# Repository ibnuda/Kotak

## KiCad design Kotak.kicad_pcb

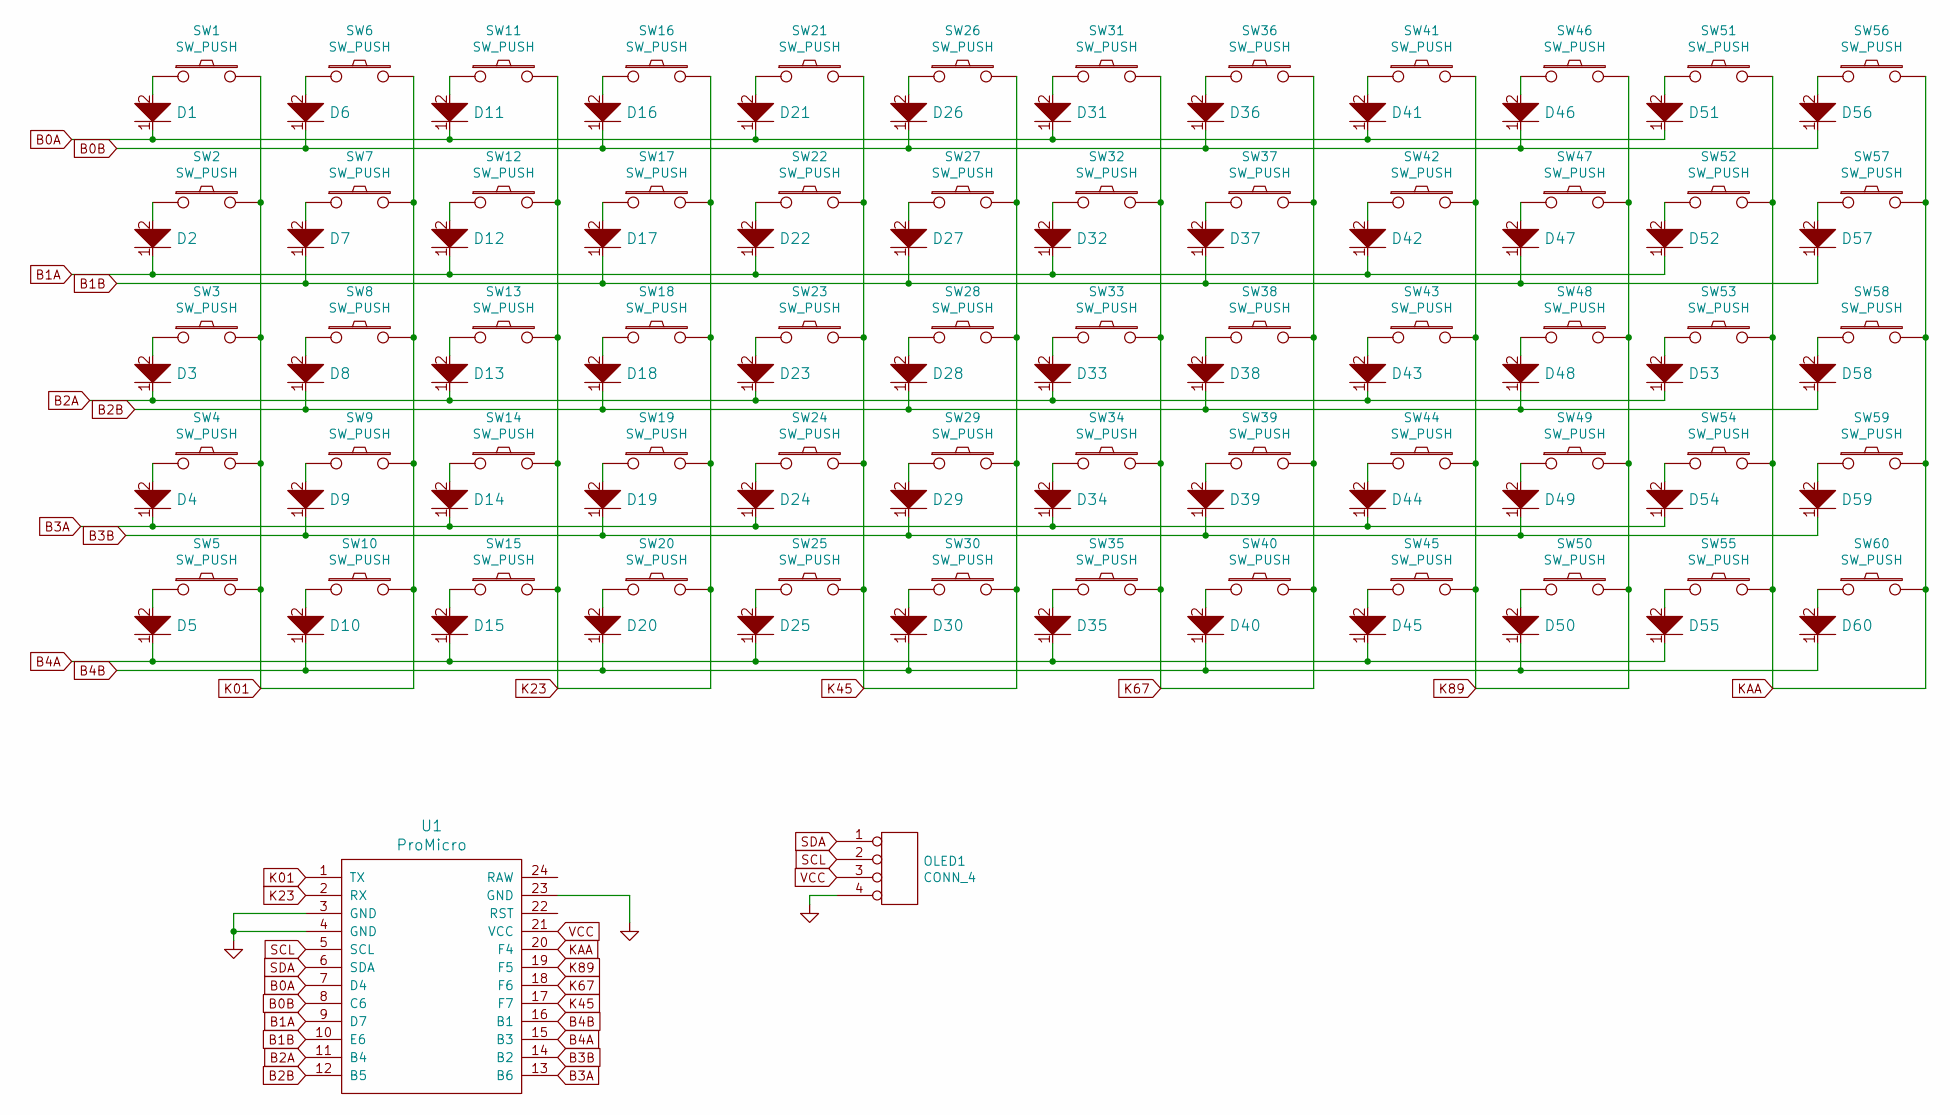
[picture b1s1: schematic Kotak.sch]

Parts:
D1, D2, D3, D4, D5, D6, D7, D8, D9, D10, D11, D12, D13, D14, D15, D16, D17, D18, D19, D20, D21, D22, D23, D24, D25, D26, D27, D28, D29, D30, D31, D32, D33, D34, D35, D36, D37, D38, D39, D40, D41, D42, D43, D44, D45, D46, D47, D48, D49, D50, D51, D52, D53, D54, D55, D56, D57, D58, D59, D60: D; Diode
OLED1: CONN_4; 1X04_NO_SILK
SW1, SW2, SW3, SW4, SW5, SW6, SW7, SW8, SW9, SW10, SW11, SW12, SW13, SW14, SW15, SW16, SW17, SW18, SW19, SW20, SW21, SW22, SW23, SW24, SW25, SW26, SW27, SW28, SW29, SW30, SW31, SW32, SW33, SW34, SW35, SW36, SW37, SW38, SW39, SW40, SW41, SW42, SW43, SW44, SW45, SW46, SW47, SW48, SW49, SW50, SW51, SW52, SW53, SW54, SW55, SW56, SW57, SW58, SW59, SW60: SW_PUSH; MX_Plate_100H
U1: ProMicro; ArduinoProMicro-ZigZag

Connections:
B0A: D1.1, D11.1, D21.1, D31.1, D41.1, D51.1, U1.7 (D4)
B0B: D6.1, D16.1, D26.1, D36.1, D46.1, D56.1, U1.8 (C6)
B1A: D2.1, D12.1, D22.1, D32.1, D42.1, D52.1, U1.9 (D7)
B1B: D7.1, D17.1, D27.1, D37.1, D47.1, D57.1, U1.10 (E6)
B2A: D3.1, D13.1, D23.1, D33.1, D43.1, D53.1, U1.11 (B4)
B2B: D8.1, D18.1, D28.1, D38.1, D48.1, D58.1, U1.12 (B5)
B3A: D4.1, D14.1, D24.1, D34.1, D44.1, D54.1, U1.13 (B6)
B3B: D9.1, D19.1, D29.1, D39.1, D49.1, D59.1, U1.14 (B2)
B4A: D5.1, D15.1, D25.1, D35.1, D45.1, D55.1, U1.15 (B3)
B4B: D10.1, D20.1, D30.1, D40.1, D50.1, D60.1, U1.16 (B1)
GND: OLED1.4, U1.3 (GND), U1.4 (GND), U1.23 (GND)
K01: SW1.2, SW2.2, SW3.2, SW4.2, SW5.2, SW6.2, SW7.2, SW8.2, SW9.2, SW10.2, U1.1 (TX)
K23: SW11.2, SW12.2, SW13.2, SW14.2, SW15.2, SW16.2, SW17.2, SW18.2, SW19.2, SW20.2, U1.2 (RX)
K45: SW21.2, SW22.2, SW23.2, SW24.2, SW25.2, SW26.2, SW27.2, SW28.2, SW29.2, SW30.2, U1.17 (F7)
K67: SW31.2, SW32.2, SW33.2, SW34.2, SW35.2, SW36.2, SW37.2, SW38.2, SW39.2, SW40.2, U1.18 (F6)
K89: SW41.2, SW42.2, SW43.2, SW44.2, SW45.2, SW46.2, SW47.2, SW48.2, SW49.2, SW50.2, U1.19 (F5)
KAA: SW51.2, SW52.2, SW53.2, SW54.2, SW55.2, SW56.2, SW57.2, SW58.2, SW59.2, SW60.2, U1.20 (F4)
unnamed: D1.2, SW1.1
unnamed: D2.2, SW2.1
unnamed: D3.2, SW3.1
unnamed: D4.2, SW4.1
unnamed: D5.2, SW5.1
unnamed: D6.2, SW6.1
unnamed: D7.2, SW7.1
unnamed: D8.2, SW8.1
unnamed: D9.2, SW9.1
unnamed: D10.2, SW10.1
unnamed: D11.2, SW11.1
unnamed: D12.2, SW12.1
unnamed: D13.2, SW13.1
unnamed: D14.2, SW14.1
unnamed: D15.2, SW15.1
unnamed: D16.2, SW16.1
unnamed: D17.2, SW17.1
unnamed: D18.2, SW18.1
unnamed: D19.2, SW19.1
unnamed: D20.2, SW20.1
unnamed: D21.2, SW21.1
unnamed: D22.2, SW22.1
unnamed: D23.2, SW23.1
unnamed: D24.2, SW24.1
unnamed: D25.2, SW25.1
unnamed: D26.2, SW26.1
unnamed: D27.2, SW27.1
unnamed: D28.2, SW28.1
unnamed: D29.2, SW29.1
unnamed: D30.2, SW30.1
unnamed: D31.2, SW31.1
unnamed: D32.2, SW32.1
unnamed: D33.2, SW33.1
unnamed: D34.2, SW34.1
unnamed: D35.2, SW35.1
unnamed: D36.2, SW36.1
unnamed: D37.2, SW37.1
unnamed: D38.2, SW38.1
unnamed: D39.2, SW39.1
unnamed: D40.2, SW40.1
unnamed: D41.2, SW41.1
unnamed: D42.2, SW42.1
unnamed: D43.2, SW43.1
unnamed: D44.2, SW44.1
unnamed: D45.2, SW45.1
unnamed: D46.2, SW46.1
unnamed: D47.2, SW47.1
unnamed: D48.2, SW48.1
unnamed: D49.2, SW49.1
unnamed: D50.2, SW50.1
unnamed: D51.2, SW51.1
unnamed: D52.2, SW52.1
unnamed: D53.2, SW53.1
unnamed: D54.2, SW54.1
unnamed: D55.2, SW55.1
unnamed: D56.2, SW56.1
unnamed: D57.2, SW57.1
unnamed: D58.2, SW58.1
unnamed: D59.2, SW59.1
unnamed: D60.2, SW60.1
SCL: OLED1.2, U1.5 (SCL)
SDA: OLED1.1, U1.6 (SDA)
VCC: OLED1.3, U1.21 (VCC)

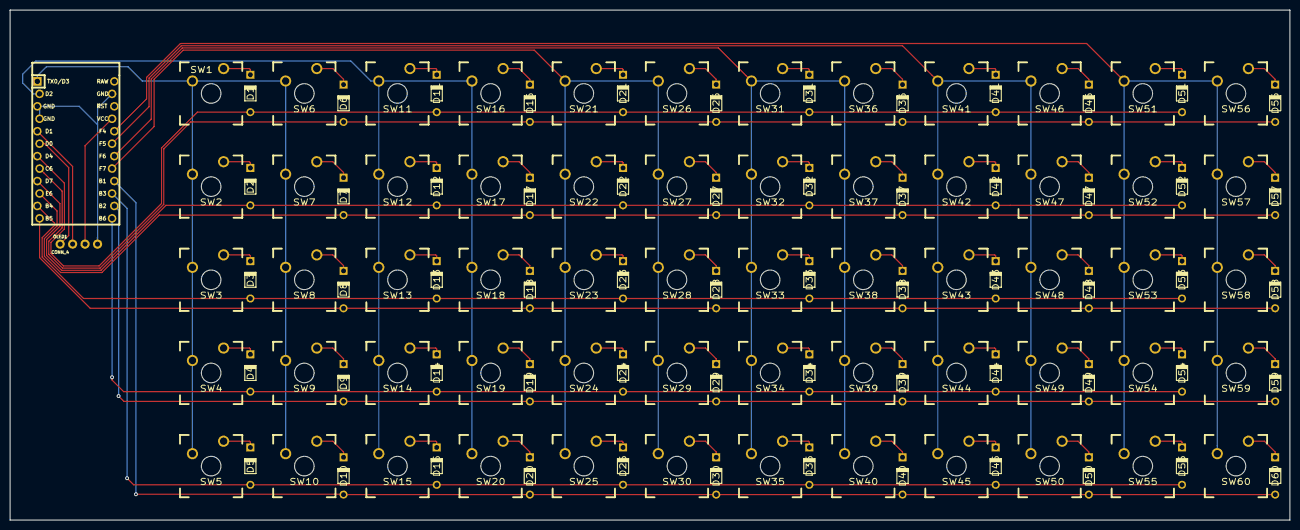
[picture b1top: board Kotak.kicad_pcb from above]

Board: 2 copper layers, 261.0 x 104.0 mm, 122 parts (0 on the bottom side), 80 nets.

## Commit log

2019-12-20 init commit.
